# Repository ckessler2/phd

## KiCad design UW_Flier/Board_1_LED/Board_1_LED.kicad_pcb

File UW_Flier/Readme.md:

Alsomitra flier manufacturing & testing info

Open NRF Connect
Launch quick start app, then under develop, launch VS Code (can't just launch from desktop)
Or (maybe) open VScode, click NRF on left bar, then dots next to project, start new terminal. 
Check if west command is recognised

Build and flash program:

cd ~/ncs/v3.1.0/zephyr/samples/basic/blinky
rm -rf build
west build -b nrf52840dk/nrf52840 --pristine

west flash

west build -b nrf52840dk/nrf52840 --pristine
west flash --dev-id 683604832

nrfjprog --snr 683604832 --readregs

west flash --dev-id 683604832

FLIER BASE STRUCTURE (Mylar, rod, glue, pins, 3D printer)

Laser cut outline with 3.6mm Mylar
Put outline, pins, and washers into printed jig
Place rod onto jig, glue and let set

Mylar - https://www.chemplex.com/150-spectrocertifiedr-thin-film-sample-support-windows-in-continuous-rolls-pre-perforated-rolls-and-precut-circles.html
Rod - https://micronwings.com/product/carbon-fibre-rod-0-25mm/
Glue - https://bsi-inc.com/hardware/hardware.html

FLIER ACTUATOR (Kapton, magnets, wire, glue, allen key, winder, microscope)

Make tube from kapton and glue (using allen key)
Using winder and glue, coil wire onto tube (30 turns 3 times for 90 coils)
Solder wires onto connectors

ELECTRONICS BOARD

Laser cut board, remove copper strips, polish contacts
Add solder balls (in fridge, put back when done) to correct contacts
Place components on solder
Turn on heat plate until solder melts

I just had a very interesting conversation with a PhD student here at UW, which I think is worth sharing - given our recent conversation about hardware requirements and how they affect verification. Chun-Cheng (chuncc@cs.washington.edu) works on on-device ML applications, and is familiar with the SoC I am using (Nordic NR52). He suggests that for this application, it makes sense to upgrade to a newer model (NR54) since it has much more memory - 1 MB compared to 64 KB with my current hardware. In his opinion, the size of network that can be run on the smaller hardware's memory will not be capable of complex pattern recognition, and therefore not be powerful or useful.

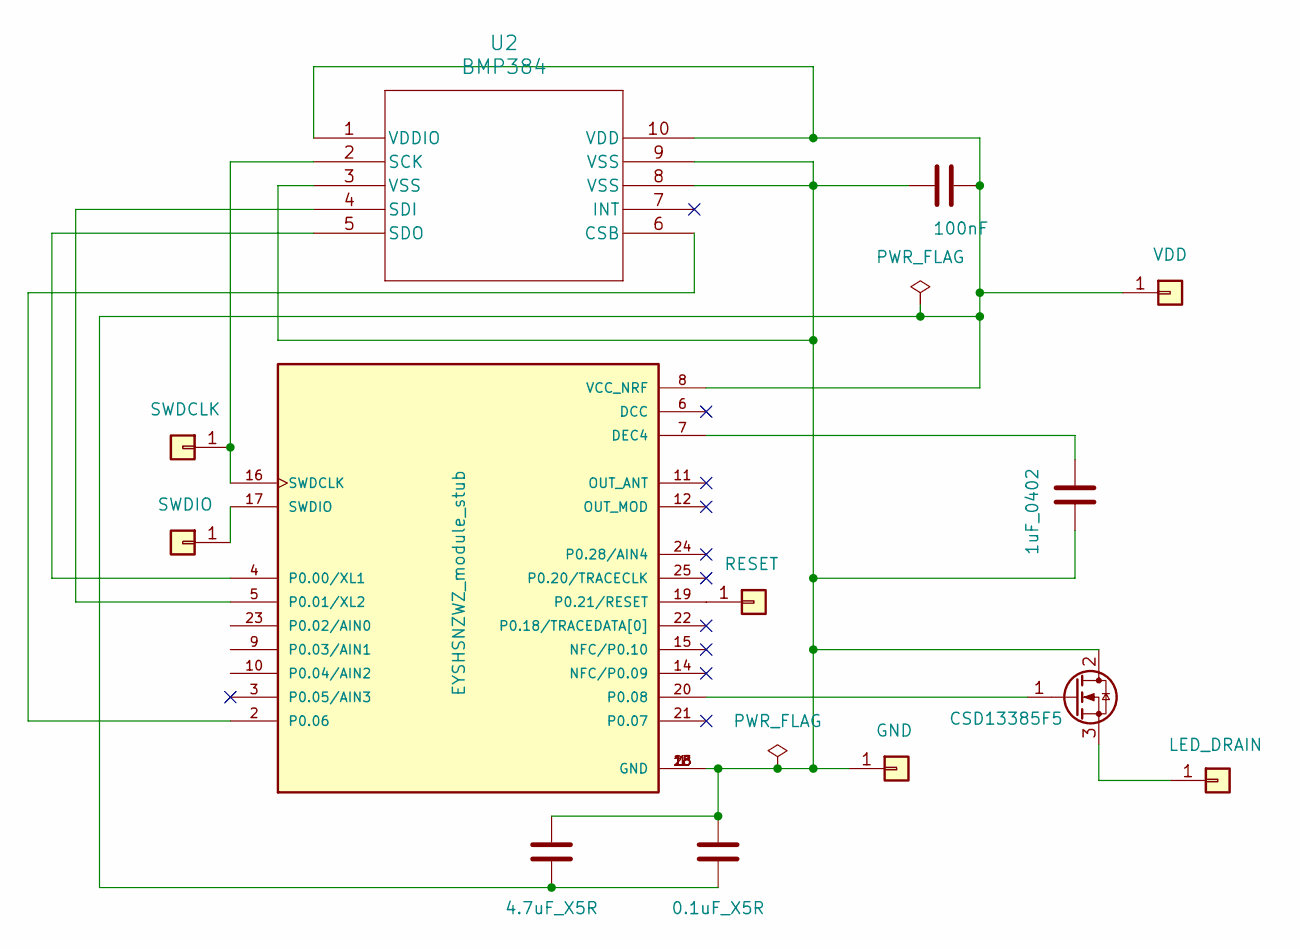
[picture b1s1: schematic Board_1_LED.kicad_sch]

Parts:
C1: 4.7uF_X5R; C_0402_1005Metric
C2: 0.1uF_X5R; C_0402_1005Metric
C3: 1uF_0402; C_0402_1005Metric
C6: 100nF; C_0402_1005Metric
J1: RESET; TestPoint_Pad_1.0x1.0mm
J2: SWDIO; TestPoint_Pad_1.0x1.0mm
J3: SWDCLK; TestPoint_Pad_1.0x1.0mm
J4: GND; TestPoint_Pad_1.0x1.0mm
J5: VDD; TestPoint_Pad_1.0x1.0mm
J6: LED_DRAIN; TestPoint_Pad_1.0x1.0mm
Q1: CSD13385F5; TRANS_CSD13385F5
U1: EYSHSNZWZ_module_stub; XCVR_EYSHSNZWZ; PARTREV 1.2
U2: BMP384; LGA10_2.0X2.0X0.95_BOS

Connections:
unnamed: J1.1, U1.19 (P0.21/RESET)
unnamed: J2.1, U1.17 (SWDIO)
unnamed: J3.1, U1.16 (SWDCLK), U2.2 (SCK)
unnamed: C1.2, C2.2, C3.2, C6.1, J4.1, Q1.2 (D), U1.1 (GND), U1.13 (GND), U1.18 (GND), U1.26 (GND), U2.3 (VSS), U2.8 (VSS), U2.9 (VSS)
unnamed: C1.1, C2.1, C6.2, J5.1, U1.8 (VCC_NRF), U2.1 (VDDIO), U2.10 (VDD)
unnamed: J6.1, Q1.3 (S)
unnamed: Q1.1 (G), U1.20 (P0.08)
unnamed: C3.1, U1.7 (DEC4)
unnamed: U1.4 (P0.00/XL1), U2.5 (SDO)
unnamed: U1.5 (P0.01/XL2), U2.4 (SDI)
unnamed: U1.2 (P0.06), U2.6 (CSB)

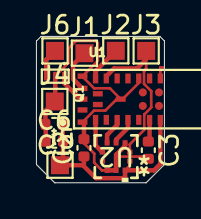
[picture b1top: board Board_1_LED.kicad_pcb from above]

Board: 2 copper layers, 7.1 x 8.1 mm, 13 parts (0 on the bottom side), 11 nets.

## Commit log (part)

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2024-10-09 updated stuff
2024-10-09 added back gaussian
2024-10-09 trained new controller
2024-10-09 set back to PID
2024-10-09 updated figures
2024-10-10 updated to not use FD
2024-10-10 fixed sys definition - now has 7 dims, 1 input
2024-10-10 fixed rendering error
2024-10-13 fixed reachability - now it crashes at t=1 instead of t=0
2024-10-14 set timestep to 0.02, total 2s
2024-10-21 changes to reachability (monday before lab)
2024-10-23 segmented input set
2024-10-30 updated alsomitra reachability for others to use
2024-10-30 deleted unnecesaty files
2024-10-30 updated hessian
2024-10-30 called plotfile at the end of reachability
2024-10-30 commented unnecesary code
2024-11-05 Reachability now works without FD hessian (16 segments)
2024-11-05 deleted unnecesary files
2024-11-05 deleted comments
2024-11-12 fixed plot
2024-11-12 re-fixed sim file
2024-11-12 put old stuff in folder for readability
2024-11-15 minor changes
2024-12-10 new trained models
2024-12-10 updated normalisation method
2024-12-10 fixed normalisation
2024-12-10 new adversarial training (PID centered)
2024-12-10 new nns
2024-12-16 added adversarial training in new folder
2024-12-19 new lipschitz robustness model
2024-12-19 removed useless models
2024-12-20 adderd folder
2024-12-20 changed name
2024-12-21 renaming, moving files to old
2025-01-10 stuff
2025-01-10 added base model
2025-01-10 base model 1000
2025-01-10 new unnormalized training dataset
2025-01-14 new networks
2025-01-16 implemented lipschitz loss (2nd time)
2025-01-17 fixed lipschitz training
2025-01-17 new lipschitz model (3k)
2025-01-19 new 0.01 (4k epochs)
2025-01-19 new 0.05, 0.02 and 0.04. Just realised that alpha = 10 (probably too high)
2025-01-19 moved to alpha=10 folder
2025-01-19 added alpha=1 folder
2025-01-19 moved base model
2025-01-19 new 0.04 (3k, alpha=1)
2025-01-19 new 0.04, 3k epochs, alpha=0.1
2025-01-19 new 0.04 (3k, alpha=10)
2025-01-19 new 0.04, 0.01. 3k epochs, alpha1
2025-01-19 new 0.04, 1k, 1
2025-01-19 new 0.01
2025-01-19 new 0.04 (test, alpha=0)
2025-01-19 new 0.04, 1k, 0.1
2025-01-20 new set (1k, alpha = 0.5)
2025-01-20 moved stuff
2025-01-20 new alpha = 1 (1k) set
2025-01-20 new alpha=2 set (1k)
2025-01-20 new data - PID sim runs till 20s
2025-01-20 new alpha=1 (20s)
2025-01-20 new alpha=1 set (1k, 20s)
2025-01-20 new 0.05
2025-01-20 new alpha=2 set
2025-01-20 new plots
2025-01-20 new alpha=10
2025-01-20 new alpha=0.1
2025-01-21 new alpha=0.5, eps = 0.08
2025-01-21 new 0.08 (alpha = 1)
2025-01-21 new base model
2025-01-21 another base model
2025-01-21 new training data, still trying to fix base model
2025-01-21 deleted broken base model
2025-01-21 renamed actual base model
2025-01-22 added vcl to alpha=1, 1st reachability plot
2025-01-22 moved vcl
2025-01-22 new vcl for troubleshooting
2025-01-22 new re-exported base model
2025-01-22 fixed data
2025-01-22 tidying up
2025-01-22 fixed vehicle error by changing onnx save function to tf2onx
2025-01-22 deleted models (can't be used with vehicle)
2025-01-22 new alpha=1 set (useable with vehicle)
2025-01-22 new alpha = 10 set
2025-01-23 minor updates, back to 3k
2025-01-25 new reachability file (R in gitignore)
2025-01-25 deleted unnecesary stuff
2025-01-25 new models, going back to 1k result
2025-01-26 stuff, got final network (0.04, 1k, 10)
2025-01-26 final set of nns
2025-01-27 updated vcl
2025-01-30 new normalised networks + vehicle spec
2025-01-30 fixed name swap
2025-01-30 new base model (definetely unnormalised)
2025-01-30 new base model (normalised)
2025-01-30 new normalised networks
2025-01-30 new models, normalised and no x/y
2025-01-30 new no_x and norm
2025-01-30 new 0.002
2025-01-30 new eps normalised results - 0.0005, 0.001, 0.002, 0.005
2025-01-31 updated check_nn_accuracy
2025-02-17 stuff (2 weeks after submission)
2025-02-17 added older vcl (lost most recent)
2025-02-17 fixed vck
2025-02-19 added chordnormal code
2025-02-28 stuff (base model still doesnt work)
2025-03-04 new testX
2025-03-04 Rename Swallow_Sensor/image1.png to Swallow_Sensor/Figues/image1.png
2025-03-04 Rename Swallow_Sensor/spec_1.png to Swallow_Sensor/Figures/spec_1.png
2025-03-04 Rename Swallow_Sensor/spec_1_10x.png to Swallow_Sensor/Figures/spec_1_10x.png
2025-03-04 Rename Swallow_Sensor/spec_image_1.png to Swallow_Sensor/Figures/spec_image_1.png
2025-03-04 Rename Swallow_Sensor/swallow_difference.png to Swallow_Sensor/Figures/swallow_difference.png
2025-03-04 Rename image1.png to image1.png
2025-03-07 laptop push
2025-03-07 pc push
2025-03-07 debugging base model
2025-03-07 testing script
2025-03-10 better base model
2025-03-10 new normalised base model
2025-03-17 new no_error folder, working up till data normalisation.
2025-03-17 new working vehicle spec for robustness (takes ages to run)
2025-03-18 new dataset, training script and ROC plot scripts
2025-03-19 fixed normalisation, to use in vehicle spec
2025-03-20 Rename Papers/CAV_reviews.md to Papers/CAV/Review_Notes.md
2025-03-20 fixed vehicle spec, main training script, added lipschitz calculation to verify counterexamples. And swallow stuff
2025-03-21 updated stuff, testing relu and smaller networks
2025-03-23 updated vehicle spec, still doesnt work
2025-03-24 stuff - vehicle spec still doesn't work, need to test individual parts. PGD seems ok
2025-03-24 Created using Colab
2025-03-24 trained models in no_error
2025-03-26 stuff + caches for vehicle issue - am uploading to marabou issues
2025-03-26 got data from jawahar, plotted in file. Now need to implement gust in Li for comparison
2025-03-27 added gust comparison
2025-03-28 new base and adversarial - testing, will send to thomas
2025-03-28 updates to gust model, still not working
2025-03-31 new no_error models
2025-03-31 new 0.005, looks better??
2025-03-31 models
2025-03-31 new models, dont ignore x and y
2025-03-31 new networks, alpha=10
2025-03-31 back to alpha=2
2025-03-31 rename
2025-03-31 stuff, still need to import relu instead of sigmoid networks
2025-04-01 new relu networks, look alright
2025-04-02 stuff, fixed reachability
2025-04-02 laptop stuff
2025-04-03 blipblop stuff
2025-04-03 stuff, still not really working
2025-04-03 fixed timeStep def
2025-04-03 improvements
2025-04-14 stuff, less than two weeks until due. Think I'm done with basic properties, just need to implement robustness then I'm done for results (unless I need to train more networks)
2025-04-14 moved files, created idx for robustness verification
2025-04-14 verification stuff
2025-04-14 new robustness definition
2025-04-14 uploaded prop 4 for report
2025-04-15 Create SAIV_Structure
2025-04-17 FINAL reachability plots, fingers crossed. At least the code looks good, still need to run properly (takes ages on office pc)
2025-04-17 extract data script
2025-04-17 removed dataset, put on google drive
2025-04-24 updated classification script - currently 38/45 for 200 epochs
2025-04-24 new classification stuff. Still not great - overfitting
2025-05-01 updated swallow classifier
2025-05-02 updated swallow sensor
2025-05-06 final 2_1 model
2025-05-06 final networks and training data
2025-06-13 chordnormal stuff
2025-06-30 Rename Robotics_Summer_Talk (6) (1).pdf to 2_Robotics_Summer_School.pdf
2025-06-30 Added Summer School Pdf
2025-08-04 created study 1 folder
2025-08-06 updated li model to send to jawahar
2025-08-06 updated l m ex study code, nearly done
2025-11-01 added Kicad project files for first board
2025-11-01 first iteration of PCB 1 (testing with mosfet / LED)
2025-11-02 cad updates. Soldered 1st board (just caps, yash's pcb)
2025-11-02 Added instructions
2025-11-05 added structure manufacturing stuff
2025-11-05 added base dxf
2025-11-05 updated PCB
2025-11-07 stuff (thursday before leaving)
2025-11-17 testing commit
2025-11-18 added alsomitra marker
2025-11-18 added bmp384
